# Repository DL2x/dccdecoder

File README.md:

This is my try at building my own dcc decoder. The code is funktional with a small PC817 Opto just hooked up to the track and an arduino, but Ive tried making a pcb for it (order is ongoing as of writing this).

There is currently no code for the PCB, as I dont yet have one of them here and cant test on it.

The PCB has support for 3 individual inputs (e.g. left rail, right rail and ac contact or overhead wire), with all of them providing power.

It does not support anything other than standard dcc, this includes no support for any analog system.

There are jumpers for connecting an AC motor: desolder both of then, then hook the 2 wires of the coil to the left and right ports and the neutral wire to the middle one. For DC motors just use the outer ones.

Feel free to contribute to this project!

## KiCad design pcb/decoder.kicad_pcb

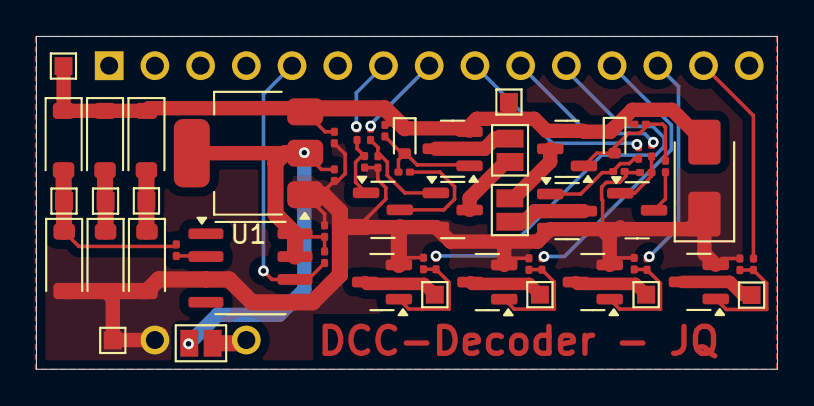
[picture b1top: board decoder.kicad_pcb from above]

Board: 2 copper layers, 41.2 x 18.5 mm, 60 parts (1 on the bottom side), 37 nets.

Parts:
A1: Arduino_Nano_v3.x; Arduino_Nano
C2, C4, C5: 100nF; C_0201_0603Metric
D1, D2, D3, D4, D5, D15: MBR120VLSFT1G; D_SOD-123
D8: SMAJ24CA; D_SMA
D11, D12: BZT585B15T-7; D_SOD-523
J1, J2, J3, J4, J5, J6, J7, J9, J11, J12: Conn_01x01_Socket; TestPoint_Pad_1.0x1.0mm
JP1, JP2, JP4: Jumper_2_Open; SolderJumper-2_P1.3mm_Open_Pad1.0x1.5mm
Q1, Q4, Q7, Q8, Q10, Q14: FDN5630; SOT-23
Q2, Q3: NTR4171P; SOT-23
Q5, Q6: BC817; SOT-23
R1: 1,3k; C_0201_0603Metric
R2, R4, R6, R11, R15, R17, R23, R31: 100k; C_0201_0603Metric
R3: 10k; C_0201_0603Metric
R5, R7, R8, R14, R16, R18, R24, R32: 100; C_0201_0603Metric
R9, R10, R12, R13: 2k; C_0201_0603Metric
U1: AMS1117; SOT-223-3_TabPin2
U3: 6N137; SOIC-8_3.9x4.9mm_P1.27mm

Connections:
/5V: C2.1, C4.2, JP1.2 (B), R3.1, U1.2 (VO), U3.7 (EN), U3.8 (VCC)
/GND: A1.29 (GND), C2.2, C4.1, C5.1, D3.2 (A), D4.2 (A), D5.2 (A), D8.1 (A1), J11.1, Q1.2 (S), Q4.2 (S), Q5.2 (E), Q6.2 (E), Q7.2 (S), Q8.2 (S), Q10.2 (S), Q14.2 (S), R2.1, R6.1, R10.2, R13.2, R15.1, R17.1, R23.1, R31.1, U1.1 (ADJ), U3.3 (C), U3.5 (GND)
/Motor_A: JP4.1 (A), Q1.3 (D)
/Motor_A1: JP4.2 (B), Q2.3 (D)
/Motor_B: JP2.2 (B), Q4.3 (D)
/Motor_B1: JP2.1 (A), Q3.3 (D)
/VM: C5.2, D1.1 (K), D2.1 (K), D8.2 (A2), D11.1 (K), D12.1 (K), D15.1 (K), J9.1, J12.1, Q2.2 (S), Q3.2 (S), R4.1, R11.2, U1.3 (VI)
unnamed: A1.27 (+5V), JP1.1 (A)
unnamed: A1.5 (D2), R3.2, U3.6 (VO)
unnamed: A1.7 (D4), R12.1
unnamed: A1.8 (D5), R14.2
unnamed: A1.9 (D6), R5.2
unnamed: A1.10 (D7), R9.1
unnamed: A1.11 (D8), R32.2
unnamed: A1.12 (D9), R24.2
unnamed: A1.13 (D10), R18.2
unnamed: A1.14 (D11), R16.2
unnamed: D1.2 (A), D4.1 (K), J5.1
unnamed: D2.2 (A), D5.1 (K), J4.1
unnamed: D11.2 (A), Q3.1 (G), R4.2, R8.2
unnamed: D12.2 (A), Q2.1 (G), R7.2, R11.1
unnamed: D3.1 (K), D15.2 (A), J6.1, R1.2
unnamed: J1.1, Q8.3 (D)
unnamed: J2.1, Q7.3 (D)
unnamed: J3.1, Q10.3 (D)
unnamed: J7.1, Q14.3 (D)
unnamed: Q1.1 (G), R2.2, R5.1
unnamed: Q4.1 (G), R6.2, R14.1
unnamed: Q5.1 (B), R9.2, R13.1
unnamed: Q5.3 (C), R7.1
unnamed: Q6.1 (B), R10.1, R12.2
unnamed: Q6.3 (C), R8.1
unnamed: Q7.1 (G), R15.2, R16.1
unnamed: Q8.1 (G), R17.2, R18.1
unnamed: Q10.1 (G), R23.2, R24.1
unnamed: Q14.1 (G), R31.2, R32.1
unnamed: R1.1, U3.2 (A)

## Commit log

2026-02-01 add code and pcb, update readme, add gitignore
2026-02-05 make PCB smaller
2026-02-05 fix gitignore not commiting
2026-02-06 fix some pcb part numbers
2026-04-24 add tests
